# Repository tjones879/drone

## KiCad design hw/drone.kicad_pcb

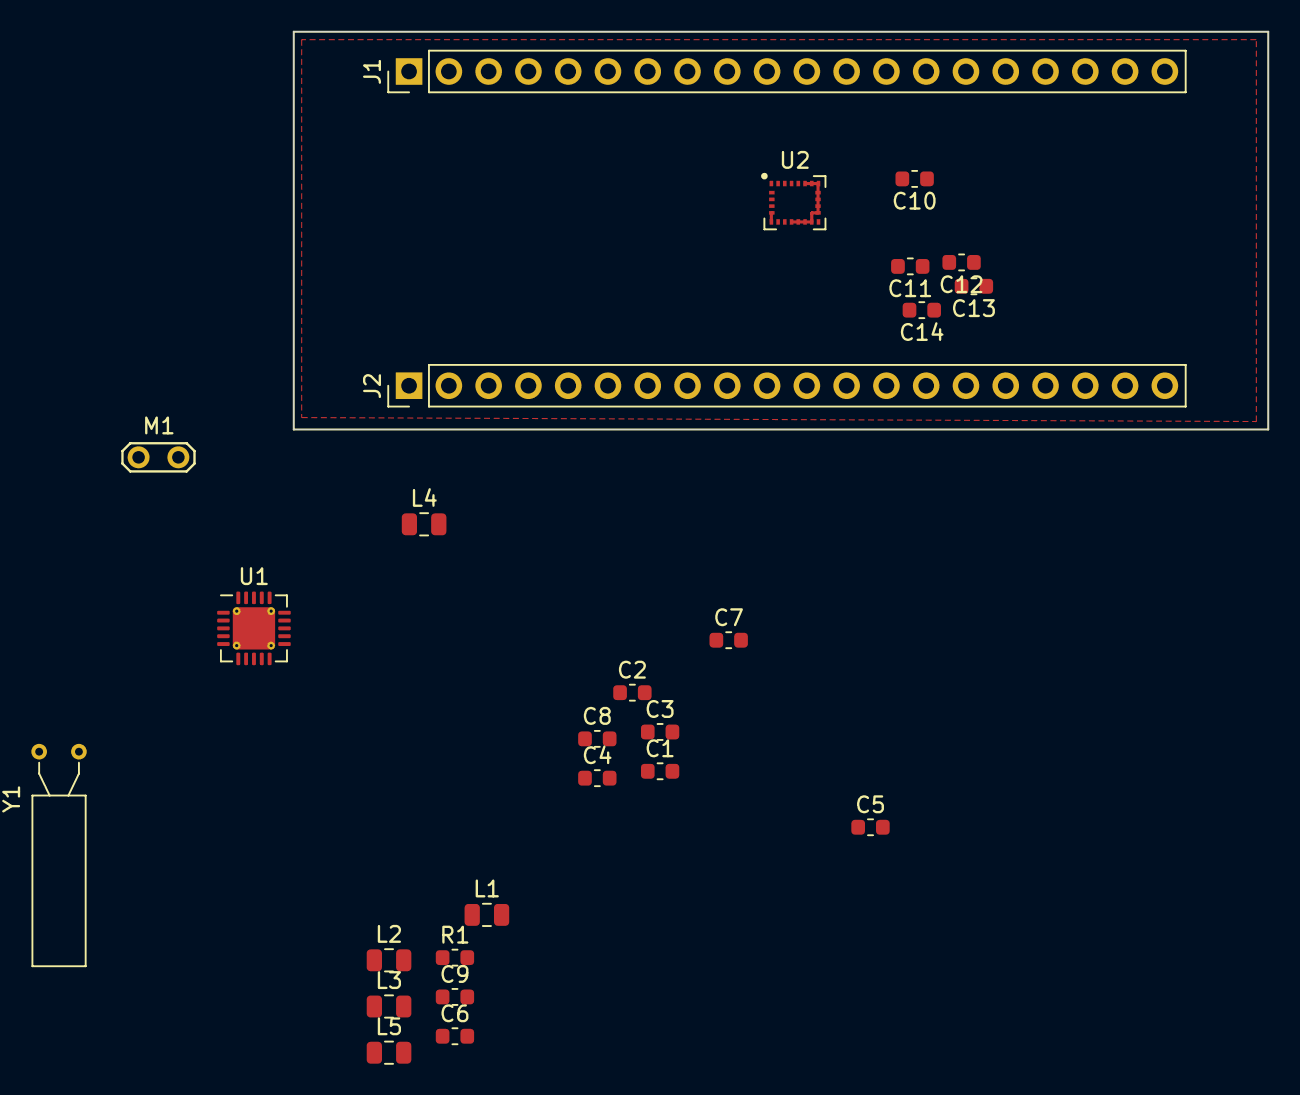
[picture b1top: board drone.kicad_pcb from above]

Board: 2 copper layers, 62.2 x 25.4 mm, 26 parts (0 on the bottom side), 24 nets.

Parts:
C1, C2, C3, C4, C5, C6, C7, C8, C9: 0.1UF-KIT-EZ-50V-20%; C_0603_1608Metric
C10, C11, C13: 100nF; C_0603_1608Metric
C12: 10nF; C_0603_1608Metric
C14: 10uF; C_0603_1608Metric
J1, J2: CONN_20; PinHeader_1x20_P2.54mm_Vertical
L1, L2, L3, L4, L5: INDUCTOR-0402-3.9NH; L_0805_2012Metric
M1: ANTENNAGPS-2X7MM; TestPoint_2Pads_Pitch2.54mm_Drill0.8mm
R1: RESISTOR0402; R_0603_1608Metric
U1: CC1101RGPR; QFN-20-1EP_4x4mm_P0.5mm_EP2.7x2.7mm_ThermalVias
U2: LSM9DS1TR; LGA-24L_3x3.5mm_P0.43mm
Y1: CRYSTALPTH-2X6; Crystal_AT310_D3.0mm_L10.0mm_Horizontal

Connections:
3.3V: U1.4, U1.9, U1.11, U1.14, U1.15
/3.3: J1.3, J2.20
/A2: J1.14, U2.8
/A3: J1.13, U2.7
/A5: J1.11, U2.2
/A6: J1.10, U2.5, U2.6
/A7: J1.9, U2.4
/G: J1.1, J1.2, J2.19
/RF/RF_N: L5.1, U1.13
/RF/RF_P: L4.1, U1.12
GND: C2.1, C4.1, C5.2, C7.1, C8.1, C9.1, C10.1, C11.2, C12.2, C13.2, C14.2, R1.1, U1.16, U1.19, U1.21, U2.9, U2.10, U2.11, U2.12, U2.14, U2.15, U2.16, U2.17, U2.18, U2.19, U2.20
unnamed: C1.1, L1.2
unnamed: C1.2, M1.1
unnamed: C2.2, L1.1, L2.2
unnamed: C3.1, C4.2, C6.1, L4.2
unnamed: C3.2, L2.1, L3.2
unnamed: C5.1, C6.2, L3.1, L5.2
unnamed: C7.2, U1.10, Y1.1
unnamed: C8.2, U1.8, Y1.2
unnamed: C9.2, U1.5
unnamed: C12.1, U2.21
unnamed: C13.1, U2.24
unnamed: R1.2, U1.17
VDD: C10.2, C11.1, C14.1, U2.1, U2.3, U2.22, U2.23

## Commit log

2019-10-11 Clear existing repo
2019-10-11 Add gitignore for kicad files
2019-10-11 Add attribute file.
2019-10-11 Add schematic files to gitattributes
2019-10-11 Add first attempt at RF schematics
2019-10-23 Create first revision of IMU sheet assign some footprints.
2019-10-27 Initial dump of flight-control SW with dependencies.
2019-10-31 Add valid footprints to most schematic symbols. Add pin headers.
2019-10-31 Add netlist and start of PCB.
2020-04-12 Partial start to PCB layout.
2020-04-19 Add micro SD schematic
2020-04-19 Add symbols to lib from micro SD.
2020-09-05 Generate empty out of tree module.
2020-09-06 Implement galois linear feedback shift register.
2020-10-03 Add libopencm3 as git submodule to flight control software
2020-10-03 Remove old rust code from flight control SW
2020-10-03 Dump progress on sensor IO
2020-10-03 Update after uart dma rename.
2020-10-05 Remove cargo build artifacts.
2020-10-06 Add DMA interface class.
2020-10-09 Use DMA interface class in UART.
2020-10-09 Add flight SW binary to gitignore.
2020-10-09 Update to most recent version of FreeRTOS.
2020-10-09 Resolve compiler warnings on header files.
2020-10-16 Add template PerhipheralRegister class.
2020-10-30 Implement initial version of YAML code generation (C++)
2020-11-27 Add a top-level C++ include for all messages.
2020-11-27 Add link to messages directory for C++ includes.
2020-11-27 Parameterize return type of peripheral registers.
2020-11-27 Create class for SPI bus handling.
2020-11-27 Create a GPIO handler class.
2020-11-27 Create a WIP LSM9DS1 class.
2020-11-27 Add messages directory to Makefile includes.
2020-11-27 Add SVC/SysTick handlers for FreeRTOS to run tasks.
2020-11-27 Add FreeRTOS task to main.
2020-11-27 Dump last copy of MPU6050 before deletion.
2020-11-27 Remove MPU6050 from use in project.
2020-11-28 Modify FreeRTOS defines for static allocation and stream_buffer.
2020-11-28 Remediate Wconversion warnings.
    static_cast to RegisterType in peripheral register after masking
    against numeric_limits<RegisterType>::max()
2020-11-28 Separate header and CPP file in C++ codegen.
2020-11-28 Add a SOFTWARE system for debug messages.
2020-11-28 Create a StaticMessageBuffer class for eventual MT-safe messagebuffer.
2020-11-28 Remove literal references to USART1 from UART device class.
2020-11-28 Fix spelling of semaphore. Add support for static mutex.
2020-11-29 Add support for serialize method in C++ codegen.
2020-11-29 Regenerate C++ files with serialize method.
2020-11-29 Add message_buffer, semaphore, codegen source files
2020-11-29 Add mutex thread safety to to message buffer class.
2020-11-29 Separate top-level header and source file templates.
2020-11-29 Add deadline-missed message. Regenerate separated top-level import.
2020-11-29 Add missing deadline-missed message from prev commit.
2020-11-29 Pull telemetry downlink task into separate header and source.
2020-11-29 Add uart::write_data_block using std::array
2020-11-29 Add missing return on move-assignment operator.
2020-11-29 Add telemetry task and messages source files. Add user flags to makefile.
2020-12-06 Move USART1 TX DMA interrupt to telemetryTask files
2020-12-06 Correctly spell semaphore include.
2020-12-06 Add read_from_peripheral mode to DMA class.
2020-12-06 Add relational operators for StrongType.
2020-12-06 Add baudrate control to UART and partially fix DMA addressing.
2020-12-06 Separate R/W mutexes from message buffer to avoid deadlock when reader is waiting.
2020-12-06 Add burst read method to I2C class.
2020-12-06 Rename GPS_MESSAGE_BUFFER_SIZE_BYTES to accurate name.
2020-12-06 Add a GPS RX task to read from USART2
2020-12-06 Add a InvalidSentence message to GNSS system.
2020-12-06 Clean up multi-line comments in C++ codegen.
2020-12-06 Regenerate with cleaner multi-line C++ comments.
2020-12-06 Add build script to automatically build all systems.
2020-12-06 Add start of code generation README
2020-12-06 Add NMEA checksum verification method with error message generation.
2020-12-07 Convert DOP statistics to floating point values.
